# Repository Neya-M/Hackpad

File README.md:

## Hackpad
FINISHED IT, DEMO HERE :D

https://github.com/user-attachments/assets/ae1be2d1-e361-4396-a303-68cf132932a8

This is my Hackpad! It has 8 buttons, 1 rotary encoder, 2 RGBs, and an OLED screen.
I made it to control music and type emoticons :)

BOM:
8x Cherry MX Switches
2x SK6812 MINI Leds
1x XIAO RP2040
8x Blank DSA Keycaps
4x M3x16 Bolt
1x EC11 Rotary encoder
1x 0.91 inch OLED displays

# Case

# Schematic

# PCB

# 3D View

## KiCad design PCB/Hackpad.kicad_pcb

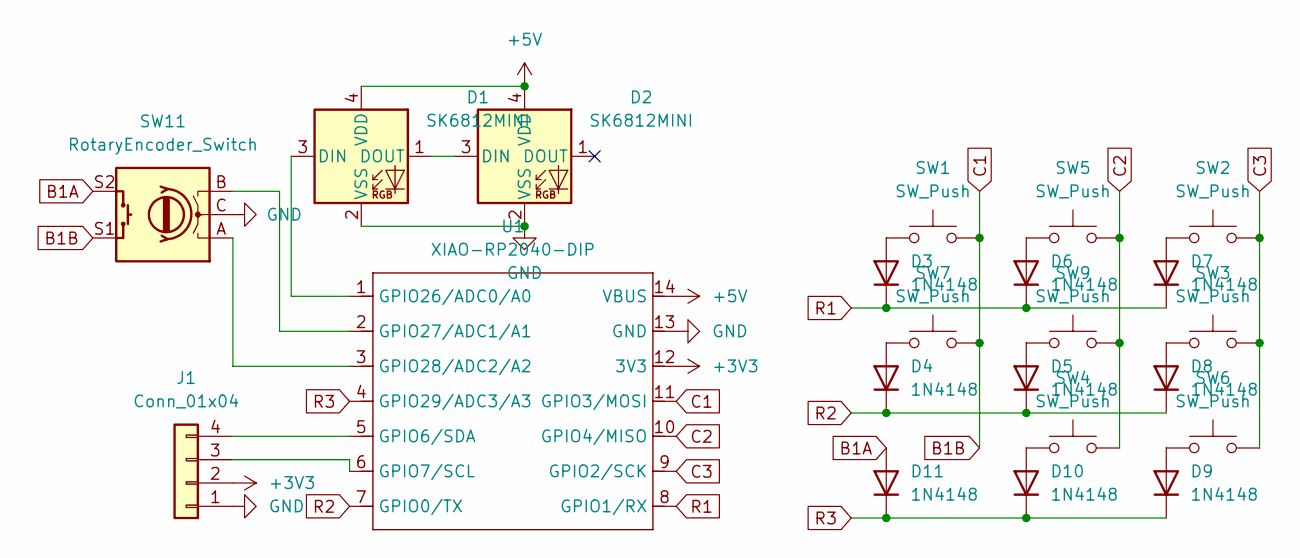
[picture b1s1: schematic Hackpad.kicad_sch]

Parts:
D1, D2: SK6812MINI; LED_SK6812MINI_PLCC4_3.5x3.5mm_P1.75mm
D3, D4, D5, D6, D7, D8, D9, D10, D11: 1N4148; D_DO-35_SOD27_P7.62mm_Horizontal
J1: Conn_01x04; SSD1306-0.91-OLED-4pin-128x32
SW1, SW2, SW3, SW4, SW5, SW6, SW7, SW9: SW_Push; SW_Cherry_MX_1.00u_PCB
SW11: RotaryEncoder_Switch; RotaryEncoder_Alps_EC12E-Switch_Vertical_H20mm
U1: XIAO-RP2040-DIP

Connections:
+3V3: J1.2, U1.12 (3V3)
+5V: D1.4 (VDD), D2.4 (VDD), U1.14 (VBUS)
B1A: D11.2 (A), SW11.S2
B1B: SW1.2, SW7.2, SW11.S1, U1.11 (GPIO3/MOSI)
C2: SW4.2, SW5.2, SW9.2, U1.10 (GPIO4/MISO)
C3: SW2.2, SW3.2, SW6.2, U1.9 (GPIO2/SCK)
GND: D1.2 (VSS), D2.2 (VSS), J1.1, SW11.C, U1.13 (GND)
unnamed: D1.3 (DIN), U1.1 (GPIO26/ADC0/A0)
unnamed: D1.1 (DOUT), D2.3 (DIN)
unnamed: D3.2 (A), SW1.1
unnamed: D4.2 (A), SW7.1
unnamed: D5.2 (A), SW9.1
unnamed: D6.2 (A), SW5.1
unnamed: D7.2 (A), SW2.1
unnamed: D8.2 (A), SW3.1
unnamed: D9.2 (A), SW6.1
unnamed: D10.2 (A), SW4.1
unnamed: J1.3, U1.6 (GPIO7/SCL)
unnamed: J1.4, U1.5 (GPIO6/SDA)
unnamed: SW11.B, U1.2 (GPIO27/ADC1/A1)
unnamed: SW11.A, U1.3 (GPIO28/ADC2/A2)
R1: D3.1 (K), D6.1 (K), D7.1 (K), U1.8 (GPIO1/RX)
R2: D4.1 (K), D5.1 (K), D8.1 (K), U1.7 (GPIO0/TX)
R3: D9.1 (K), D10.1 (K), D11.1 (K), U1.4 (GPIO29/ADC3/A3)

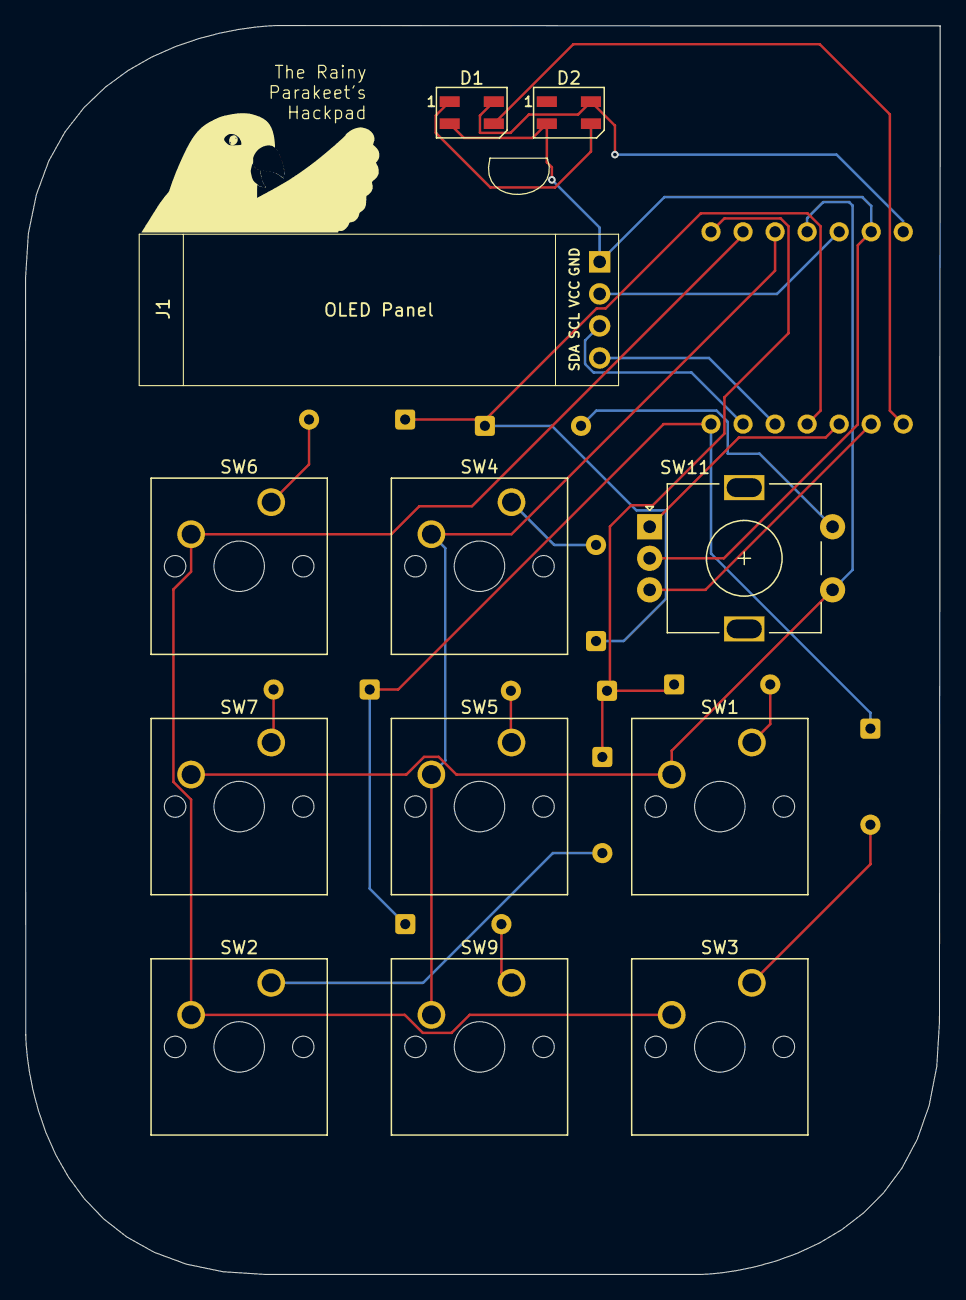
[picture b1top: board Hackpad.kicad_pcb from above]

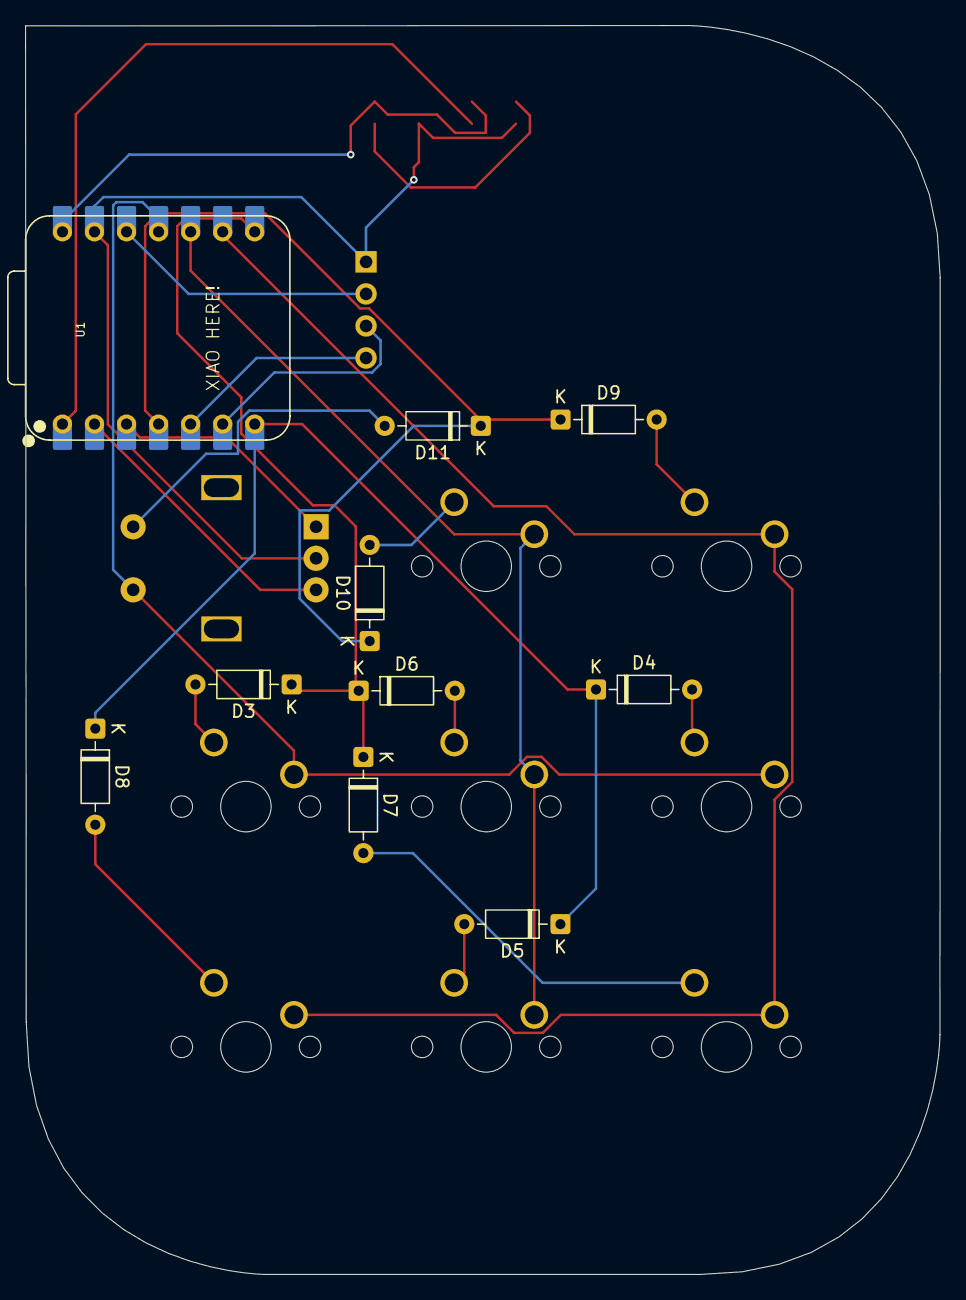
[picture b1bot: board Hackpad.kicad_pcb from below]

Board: 2 copper layers, 72.5 x 99.0 mm, 22 parts (10 on the bottom side), 24 nets.

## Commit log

2025-07-07 reorganize files
2025-07-08 reorganize
2025-07-08 reorganize firmware
2026-03-29 Add demo
2026-03-29 Rename IMG-3336.mp4 to demo.mp4
